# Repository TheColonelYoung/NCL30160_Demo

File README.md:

# NCL30160_Demo
Demonstration board for light control IC NCL30160.

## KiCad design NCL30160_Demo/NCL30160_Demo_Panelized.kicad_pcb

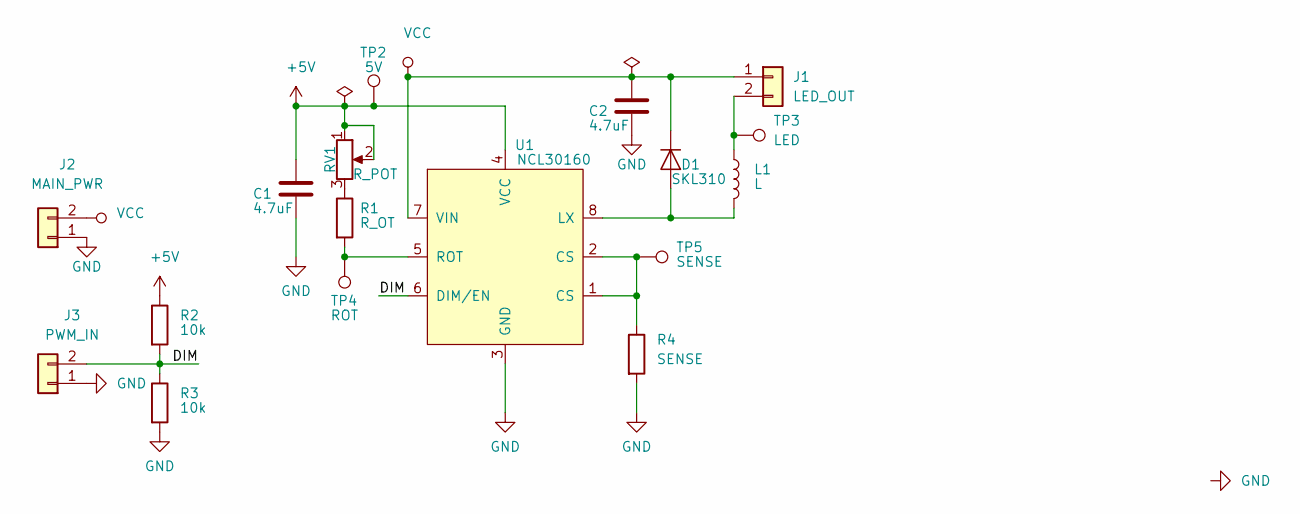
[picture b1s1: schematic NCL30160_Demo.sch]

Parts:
C1, C2: 4.7uF; C_0805_2012Metric
D1: SKL310; D_SOD-123F
J1: LED_OUT; Wire_2_SMD_2x3mm
J2: MAIN_PWR; Wire_2_SMD_2x3mm
J3: PWM_IN; Wire_2_SMD_2x3mm
L1: L; L_Taiyo-Yuden_NR-80xx
R1: R_OT; R_0603_1608Metric
R2, R3: 10k; R_0603_1608Metric
R4: SENSE; R_1206_3216Metric
RV1: R_POT; Potentiometer_Bourns_3214J_Horizontal
TP2: 5V; TestPoint_Pad_D1.0mm
TP3: LED; TestPoint_Pad_D1.0mm
TP4: ROT; TestPoint_Pad_D1.0mm
TP5: SENSE; TestPoint_Pad_D1.0mm
U1: NCL30160; SOIC-8_3.9x4.9mm_P1.27mm

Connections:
+5V: C1.1, R2.1, RV1.1, RV1.2, TP2.1, U1.4 (VCC)
/DIM: J3.2, R2.2, R3.1, U1.6 (DIM/EN)
GND: C1.2, C2.2, J2.1, J3.1, R3.2, R4.2, U1.3 (GND)
unnamed: D1.2 (A), L1.2, U1.8 (LX)
unnamed: J1.2, L1.1, TP3.1
unnamed: R1.1, RV1.3
unnamed: R1.2, TP4.1, U1.5 (ROT)
unnamed: R4.1, TP5.1, U1.1 (CS), U1.2 (CS)
VCC: C2.1, D1.1 (K), J1.1, J2.2, U1.7 (VIN)

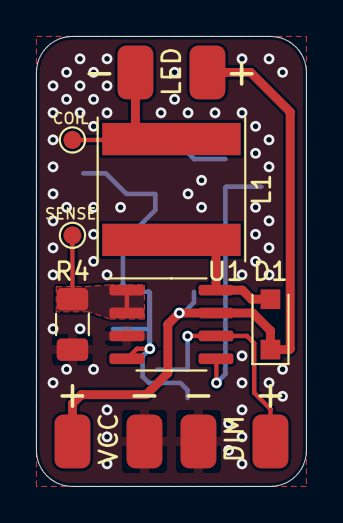
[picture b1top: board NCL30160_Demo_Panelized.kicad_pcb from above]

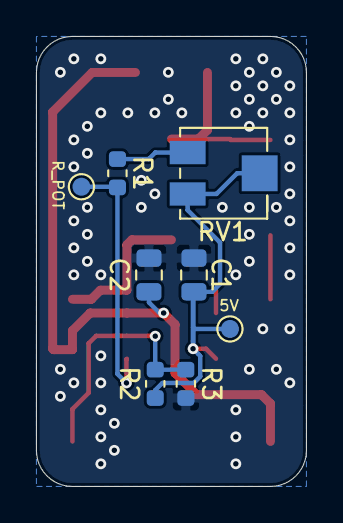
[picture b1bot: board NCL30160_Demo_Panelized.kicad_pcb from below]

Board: 2 copper layers, 15.0 x 25.0 mm, 17 parts (8 on the bottom side), 9 nets.

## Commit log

2020-02-03 Schema: create schema of demo board
2020-02-03 doc: add documentation including calculation spreasheet and presentation of IC
2020-02-26 PCB: routing of PCB
2020-02-26 PCB: generate panelized variant of board 4x6 pcs
